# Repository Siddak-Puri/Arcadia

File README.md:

# Arcadia
Arcadia is an emulation console built on an old laptop’s motherboard that runs games from Retroarch's cores. The custom controller connects to the mother board using a wired Raspberry Pi Pico based controller made on an XBOX controller layout. The end goal of Arcadia is to make games of various retro consoles playable at a single machine using any controller.

It supports the following consoles:-
- SNES
- NES
- N64
- GBA
- NDS
- WII
- Gamecube
- CPS3
- Dreamcast
- 32X
- Genesis
- Megadrive
- Saturn
- PS
- PSP
- PS2

## UI images
**Title Screen(Animations)**

https://github.com/user-attachments/assets/efa5a282-93ec-4039-b4d3-f5487ecb250c

**Loading Screen**

**Main Screen (designed on figma)**

## Console Design(with storage compartment)

# Controller

## Controller Images

**Controller Cad(1st week)**

**Controller Cad(2nd week)**

**Controller Cad**(3rdweek)

pcb mount (to clean up after i learn form modelling)
## Controller Description
- **The controller consists of two alps alpine joysticks(ALPSALPINE RKJXV1224005)** with **digital tactile switches** for menu, view, home, reset etc. It also contains **4 right angled trigger buttons** (XKB Connection TC-1102N-C-DL-B) for LB, LT, RB, RT. + 8 more tactile buttons for X, Y, B, A and D-Pad.
- The controller runs with a raspberry pi pico which is mounted on the left side of the controller pcb
--- 
## Hardware Requirements
* Raspberry Pi Pico (RP2040)
* 1x Controller main PCB + 2x shoulder PCBs
* 2x Alps RKJXV1224005 analog joysticks
* 1x MCP3008-I/P ADC (DIP-16) + DIP-16 socket
* 12x 6x6 mm tactile switches (D-pad, ABXY, Menu, View, Home, Reset)
* 4x TC-1102N-C-DL-B right-angle tactile switches (LB, LT, RB, RT)
* 2x 100 nF ceramic capacitors
* 4x JST-XH 3-pin headers (B3B-XH-A) + 2x JST-XH 3-pin cables (straight-through)
* 4x M3 screws (main board) + 2x M2 screws (shoulder boards)
* Micro-USB cable
* 3D printed shell and button caps (PLA/PETG recommended)

## PCB Architecture and design plus VERSION 1 of Controller design:
**Schematic diagram of main PCB**

**PCB diagram of main PCB**

Most beautiful creation by me :) 

**Main PCB in 3D viewer**

**Schematic diagram of Shoulder Board(LT,LB,RT,RB)**

**PCB diagram of shoulder PCB**

**Shoulder PCB in 3D Viewer**

**Reference for future controller design**

## Week 2 progress on controller:
In week 2, the bumper buttons rt,rb,lt,lb were changed to be analog, two dual shock motors to get haptic feedback and make the user feel emerged in the game (connectors were used for dual shock motors), then the pcb board was made by researching different fusion 360 tool and then mounting and routing components on the new board design followed by ground pour and then pcb mount was made to hold pcb within. Also form modelling was learnt

## What to expect from the next week:
- Controller FULLY done with form tool (to make it more like ergonomic modern day controllers).
- Firmware written from scratch.

## How do these boards connect/will connect to the 3d model:
There will be two copies used of shoulder board one for LB and LT and another for RB and RT and they will be tilted inwards at an angle of 45 degree and will be attached to the main PCB.

## Pin Map

### Buttons
| Button | Pico GPIO |
|---|---|
| A | GPIO10 |
| B | GPIO9 |
| X | GPIO8 |
| Y | GPIO7 |
| LB | GPIO6 (via J1) |
| LT | GPIO5 (via J1) |
| RB | GPIO4 (via J2) |
| RT | GPIO3 (via J2) |
| View | GPIO0 |
| Home | GPIO1 |
| Menu | GPIO2 |
| D-pad Up | GPIO14 |
| D-pad Down | GPIO13 |
| D-pad Left | GPIO12 |
| D-pad Right | GPIO11 |
| L3 (left stick click) | GPIO26 |
| R3 (right stick click) | GPIO27 |
| Reset | RUN (pin 30) |

All buttons are active-low (internal pull-ups, other side to GND).

### Joysticks (via MCP3008)
| Axis | MCP3008 channel |
|---|---|
| Left stick X | CH0 |
| Left stick Y | CH1 |
| Right stick X | CH2 |
| Right stick Y | CH3 |

### MCP3008 SPI
| MCP3008 pin | Pico GPIO |
|---|---|
| DOUT (12) | GPIO16 (SPI0 RX) |
| CS (10) | GPIO17 |
| CLK (13) | GPIO18 (SPI0 SCK) |
| DIN (11) | GPIO19 (SPI0 TX) |

### Shoulder board connectors (JST-XH)
| Connector | Pin 1 | Pin 2 | Pin 3 |
|---|---|---|---|
| J1 (left) | GND | LB (GPIO6) | LT (GPIO5) |
| J2 (right) | GND | RB (GPIO4) | RT (GPIO3) |

## File Structure

Arcadia/

├── Cad(stil under development)/                  # Fusion 360 model, assembly to be finished by next week.

├── Kicad/       # KiCad project files with their step models.

├── firmware/                 # Control software for the Raspberry Pi Pico controller written in arduino IDE.

├── Gerber files             # Gerber files for PCB manufacturing.

└── README.md             # Project documentation.

# Backend
The whole backend of our project runs on python and javascript.

## Explanation File by File
1. main.py, loading.js :-
  - It is the main core of emulator it will act as the 'OS' , acting as a bridge between the games and the     frontend.
  - It uses pywebview to convert the web ui into a desktop app which is the set as the default screen of the   linux system much like the desktop of a windows or mac.
  - Subprocess is used for gathering environmental variables, reboot and shutdown.
  - It also scans the rom directory for game files, LauncherAPI keeps scanning for rom files.
  - The games run straight from the app not any external launcher app.

2. index.html :-
  - The main UI file of the whole project rendered by the pywebview.
  - Bridges the user events and display all the data to the user.
    
3. loading.css , main.css , style.css :-
  - for styling.

4. main.js :-
  - smooth scroll, page transitions(glitch) and event listeners for navigation.
5. keyboard.js :-
  - for controlling the ui using keyboard.
6. gamepad.js :-
  - for controlling the ui using gamepad.
7. Learning Part(DIR) :-
  - files we made while learning each of the features for this project.

## Credits:
Made by **thenobrainers** -- Rishu, Araadh and Siddak with love ❤️.

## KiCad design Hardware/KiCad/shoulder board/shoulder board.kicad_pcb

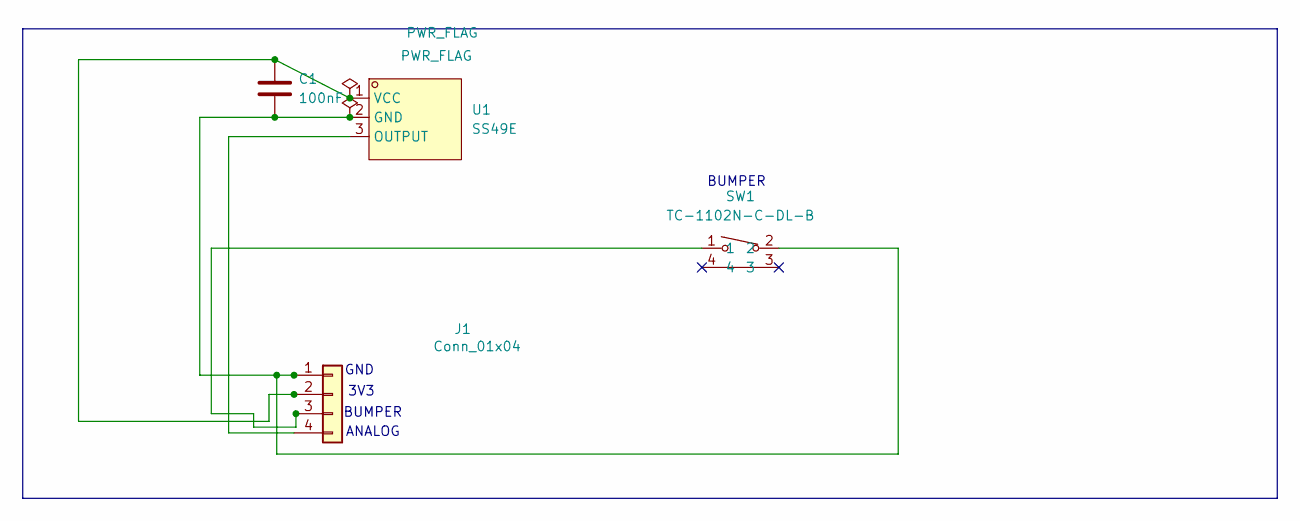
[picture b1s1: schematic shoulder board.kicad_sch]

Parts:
C1: 100nF; C_Disc_D5.0mm_W2.5mm_P2.50mm
J1: Conn_01x04; JST_XH_B4B-XH-A_1x04_P2.50mm_Vertical
SW1: TC-1102N-C-DL-B; SW-TH_TC-1102N-C-DL-B; MPN TC-1102N-C-DL-B; LCSC Part C406162
U1: SS49E; TO-92_Inline_Wide; MPN SS49E; LCSC Part C85697

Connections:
unnamed: C1.1, J1.1, SW1.2, U1.2 (GND)
unnamed: C1.2, J1.2, U1.1 (VCC)
unnamed: J1.3, SW1.1
unnamed: J1.4, U1.3 (OUTPUT)

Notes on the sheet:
GND
BUMPER
3V3
ANALOG

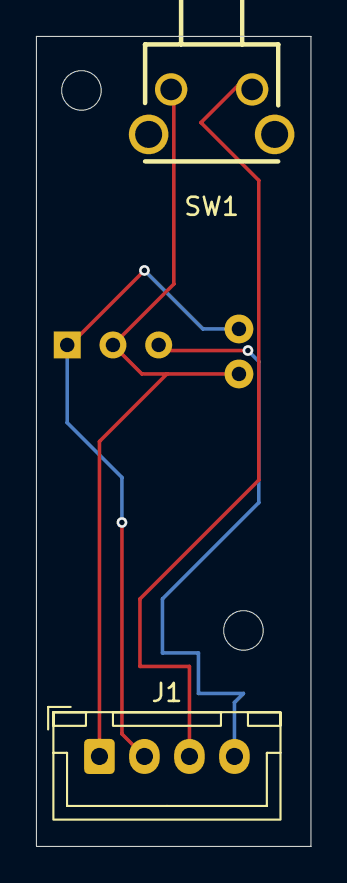
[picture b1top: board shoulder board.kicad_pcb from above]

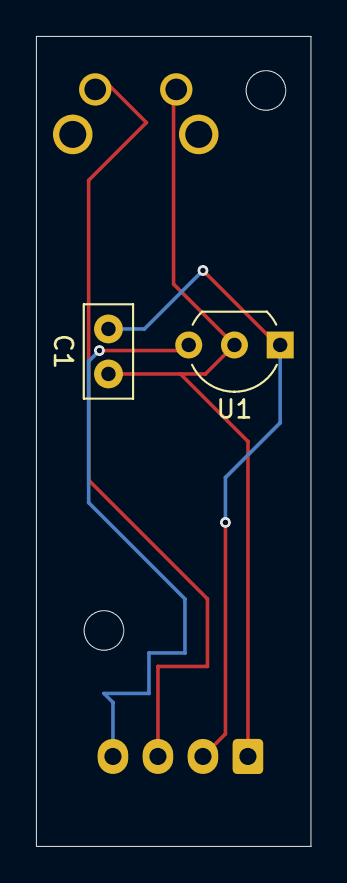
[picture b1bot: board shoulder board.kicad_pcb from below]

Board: 2 copper layers, 15.2 x 45.0 mm, 4 parts (2 on the bottom side), 4 nets.

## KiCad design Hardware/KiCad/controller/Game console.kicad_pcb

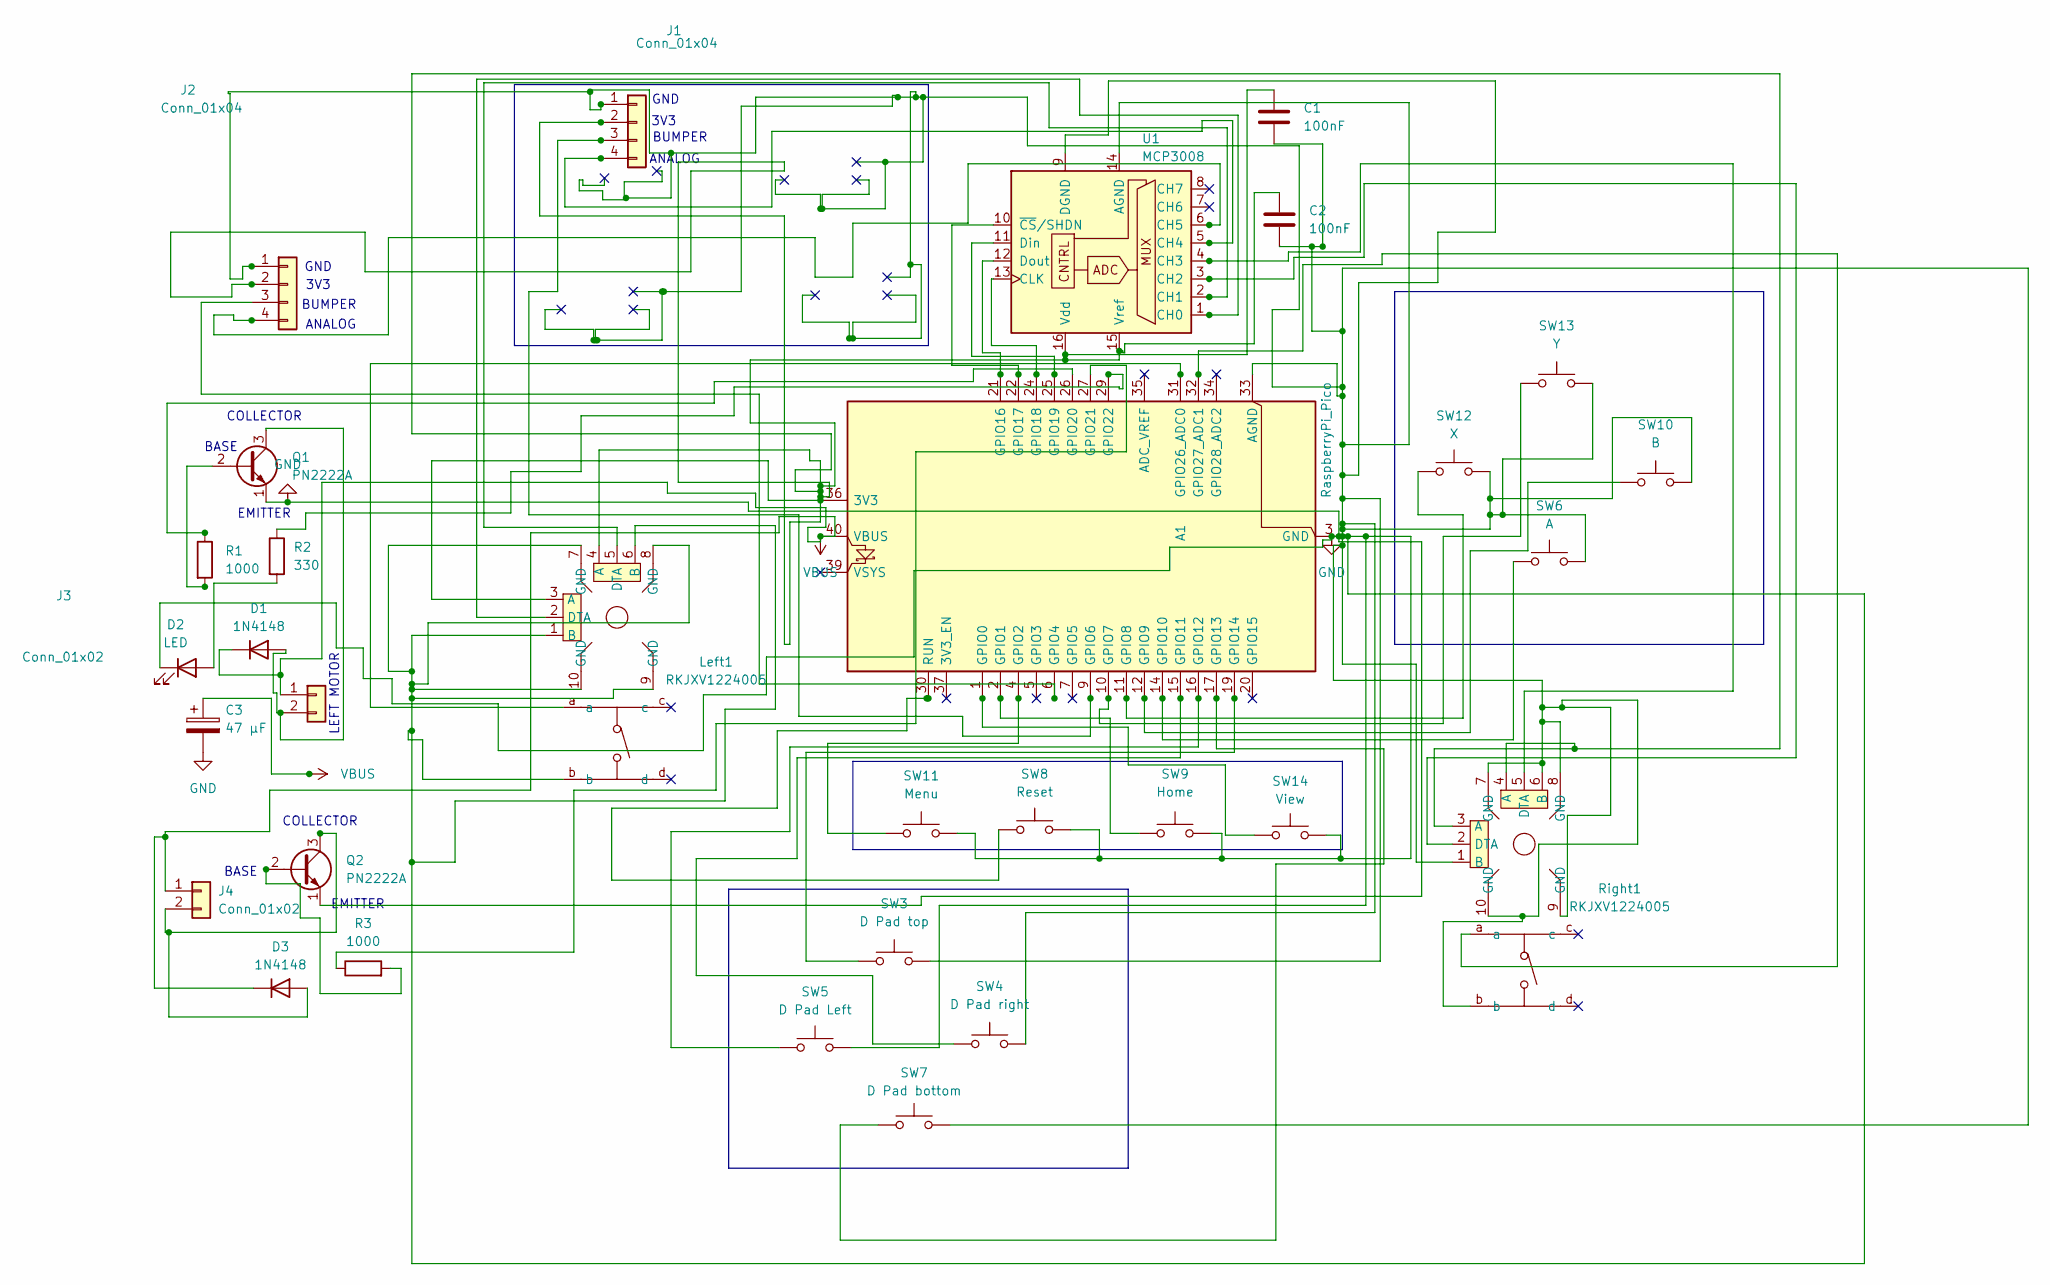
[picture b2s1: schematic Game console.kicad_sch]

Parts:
A1: RaspberryPi_Pico; RaspberryPi_Pico_Common_THT
C1, C2: 100nF; C_Disc_D5.0mm_W2.5mm_P2.50mm
C3: 47 µF; CP_Radial_D5.0mm_P2.00mm
D1, D3: 1N4148; D_DO-35_SOD27_P7.62mm_Horizontal
D2: LED; LED_D3.0mm
J1, J2: Conn_01x04; JST_XH_B4B-XH-A_1x04_P2.50mm_Vertical
J3, J4: Conn_01x02; JST_PH_B2B-PH-K_1x02_P2.00mm_Vertical
Left1: RKJXV1224005; SW-TH_RKJXV1224005; MPN RKJXV1224005; LCSC Part C146170
Q1, Q2: PN2222A; TO-92_Inline
R1, R3: 1000; R_Axial_DIN0207_L6.3mm_D2.5mm_P10.16mm_Horizontal
R2: 330; R_Axial_DIN0207_L6.3mm_D2.5mm_P10.16mm_Horizontal
Right1: RKJXV1224005; SW-TH_RKJXV1224005; MPN RKJXV1224005; LCSC Part C146170
SW3: D Pad top; SW_PUSH_6mm_H5mm
SW4: D Pad right; SW_PUSH_6mm_H5mm
SW5: D Pad Left; SW_PUSH_6mm_H5mm
SW6: A; SW_PUSH_6mm_H5mm
SW7: D Pad bottom; SW_PUSH_6mm_H5mm
SW8: Reset; SW_PUSH_6mm_H5mm
SW9: Home; SW_PUSH_6mm_H5mm
SW10: B; SW_PUSH_6mm_H5mm
SW11: Menu; SW_PUSH_6mm_H5mm
SW12: X; SW_PUSH_6mm_H5mm
SW13: Y; SW_PUSH_6mm_H5mm
SW14: View; SW_PUSH_6mm_H5mm
U1: MCP3008; DIP-16_W7.62mm

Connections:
GND: A1.3 (GND), A1.8 (GND), A1.13 (GND), A1.18 (GND), A1.23 (GND), A1.28 (GND), A1.33 (AGND), A1.38 (GND), C1.2, C2.2, C3.2, D2.1 (K), J1.1, J2.1, Left1.1 (B), Left1.6 (B), Left1.7 (GND), Left1.8 (GND), Left1.9 (GND), Left1.10 (GND), Left1.b, Q1.1 (E), Q2.1 (E), Right1.1 (B), Right1.6 (B), Right1.7 (GND), Right1.8 (GND), Right1.9 (GND), Right1.10 (GND), Right1.b, SW3.2, SW4.2, SW5.2, SW6.2, SW7.2, SW8.2, SW9.2, SW10.2, SW11.2, SW12.2, SW13.2, SW14.2, U1.9 (DGND), U1.14 (AGND)
unnamed: A1.36 (3V3), C1.1, C2.1, J1.2, J2.2, Left1.3 (A), Left1.4 (A), Right1.3 (A), Right1.4 (A), U1.15 (Vref), U1.16 (Vdd)
unnamed: A1.1 (GPIO0), SW14.1
unnamed: A1.2 (GPIO1), SW9.1
unnamed: A1.4 (GPIO2), SW11.1
unnamed: A1.6 (GPIO4), J2.3
unnamed: A1.9 (GPIO6), J1.3
unnamed: A1.10 (GPIO7), SW13.1
unnamed: A1.11 (GPIO8), SW12.1
unnamed: A1.12 (GPIO9), SW10.1
unnamed: A1.14 (GPIO10), SW6.1
unnamed: A1.15 (GPIO11), SW4.1
unnamed: A1.16 (GPIO12), SW5.1
unnamed: A1.17 (GPIO13), SW7.1
unnamed: A1.19 (GPIO14), SW3.1
unnamed: A1.21 (GPIO16), U1.12 (Dout)
unnamed: A1.22 (GPIO17), U1.10 (~CS/SHDN)
unnamed: A1.24 (GPIO18), U1.13 (CLK)
unnamed: A1.25 (GPIO19), U1.11 (Din)
unnamed: A1.26 (GPIO20), R1.1
unnamed: A1.27 (GPIO21), R3.1
unnamed: A1.29 (GPIO22), R2.1
unnamed: A1.31 (GPIO26_ADC0), Left1.a
unnamed: A1.32 (GPIO27_ADC1), Right1.a
unnamed: A1.30 (RUN), SW8.1
unnamed: D1.2 (A), J3.2, Q1.3 (C)
unnamed: D2.2 (A), R2.2
unnamed: D3.2 (A), J4.2, Q2.3 (C)
unnamed: J1.4, U1.5 (CH4)
unnamed: J2.4, U1.6 (CH5)
unnamed: Q1.2 (B), R1.2
unnamed: Q2.2 (B), R3.2
unnamed: Left1.2 (DTA), U1.1 (CH0)
unnamed: Left1.5 (DTA), U1.2 (CH1)
unnamed: Right1.2 (DTA), U1.3 (CH2)
unnamed: Right1.5 (DTA), U1.4 (CH3)
VBUS: A1.40 (VBUS), C3.1, D1.1 (K), D3.1 (K), J3.1, J4.1

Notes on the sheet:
EMITTER
GND
BUMPER
ANALOG
LEFT MOTOR
COLLECTOR
BASE
3V3

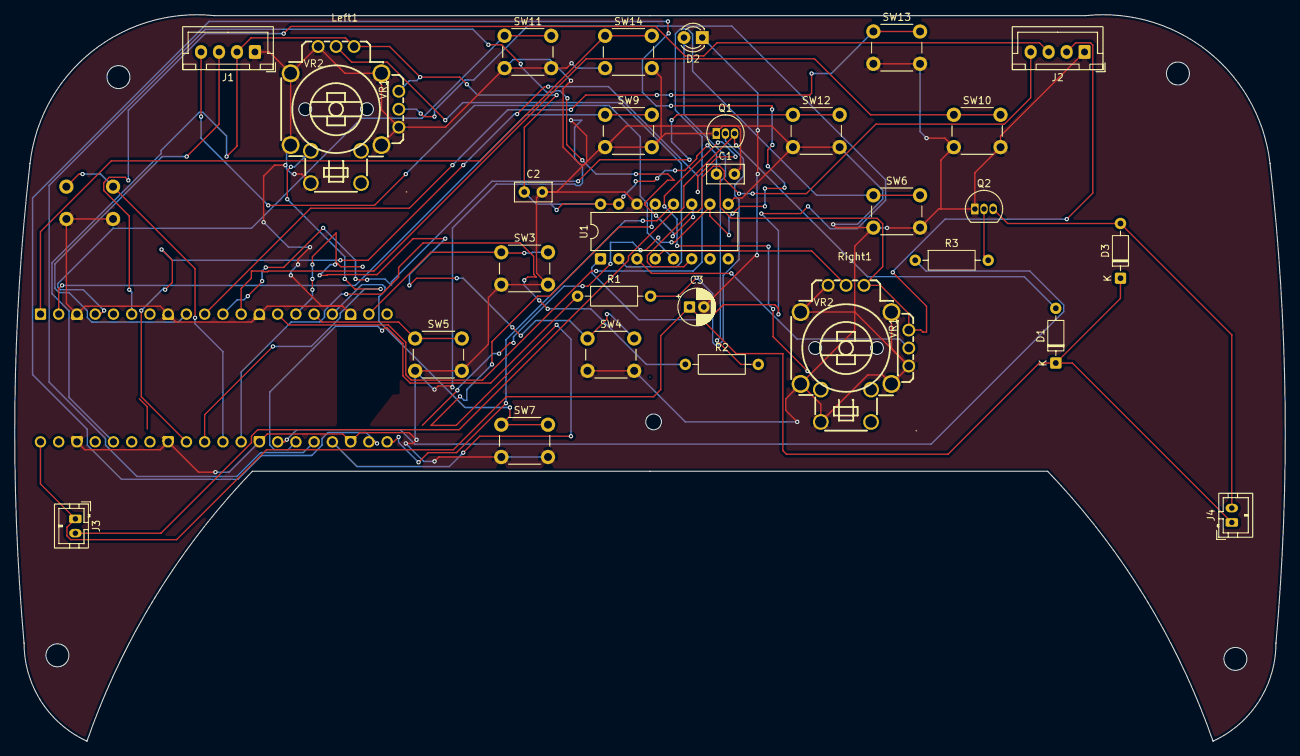
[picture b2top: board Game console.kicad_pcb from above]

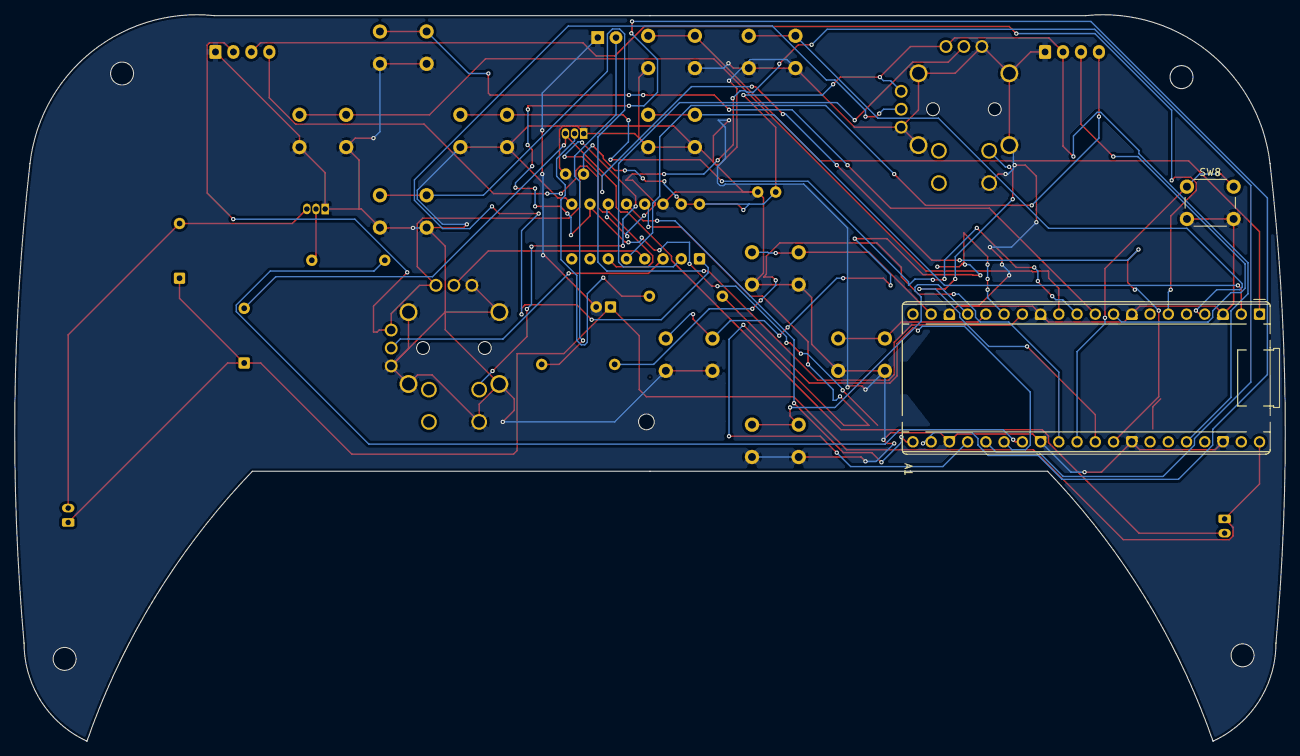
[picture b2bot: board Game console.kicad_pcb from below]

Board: 2 copper layers, 176.9 x 101.1 mm, 31 parts (2 on the bottom side), 37 nets.
